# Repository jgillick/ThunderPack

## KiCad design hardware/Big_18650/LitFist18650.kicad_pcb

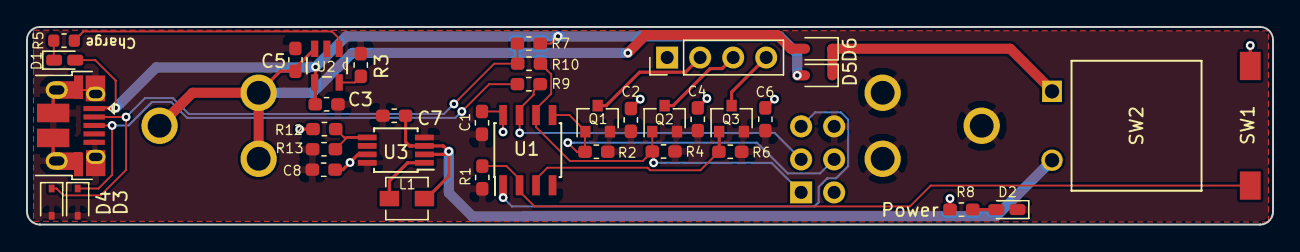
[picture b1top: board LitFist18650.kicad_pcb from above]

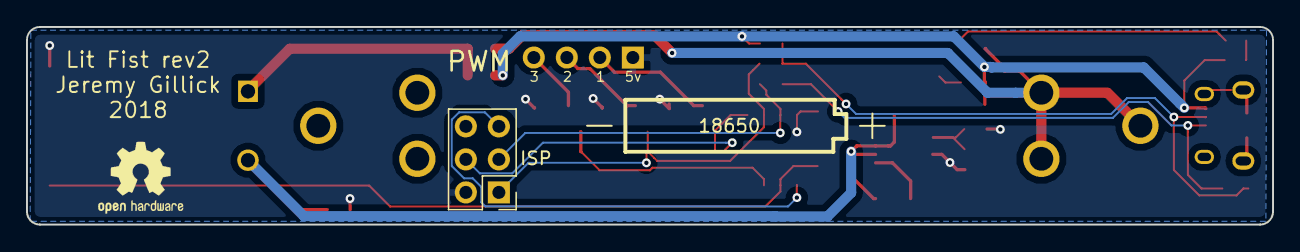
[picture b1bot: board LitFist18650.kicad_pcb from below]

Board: 2 copper layers, 95.8 x 15.2 mm, 39 parts (2 on the bottom side), 23 nets.

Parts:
C1: 0.1uF; C_0603_1608Metric_Pad1.05x0.95mm_HandSolder
C2, C3, C4, C5, C6: 4.7uF; C_0603_1608Metric_Pad1.05x0.95mm_HandSolder
C7: 10uF; C_0603_1608Metric_Pad1.05x0.95mm_HandSolder
C8: 22uF; C_0603_1608Metric_Pad1.05x0.95mm_HandSolder
D1, D2: LED; LED_0603_1608Metric_Castellated
D3, D4: 3v6; D_SOD-323
D5, D6: 20V2A; D_SOD-323
J1: PWM; PinHeader_1x04_P2.54mm_Vertical
J2: USB_B_Micro; USB_Micro-B_Amphenol_10103594-0001LF_Horizontal
J3: Battery; Battery_Clips_18650
J4: ISP; PinHeader_2x03_P2.54mm_Vertical
L1: 2.2uH3A; L_Vishay_IHLP-1212
Q1, Q2, Q3: NTR4003NT1G; SOT-23
R1: 20K; R_0603_1608Metric_Pad1.05x0.95mm_HandSolder
R2, R4, R6: 20k; R_0603_1608Metric_Pad1.05x0.95mm_HandSolder
R3: 2k; R_0603_1608Metric_Pad1.05x0.95mm_HandSolder
R5: 470; R_0603_1608Metric
R7: 2.2k; R_0603_1608Metric_Pad1.05x0.95mm_HandSolder
R8: 120; R_0603_1608Metric_Pad1.05x0.95mm_HandSolder
R9, R10: 68; R_0603_1608Metric_Pad1.05x0.95mm_HandSolder
R12: 750K; R_0603_1608Metric_Pad1.05x0.95mm_HandSolder
R13: 100K; R_0603_1608Metric_Pad1.05x0.95mm_HandSolder
SW1: Mode; Switch_TE_FSMSM
SW2: Power; Switch_SPST_GPTS203211BR2
U1: ATtiny85-20SU; SOIC-8_3.9x4.9mm_P1.27mm
U2: MCP73831T-2ACI/OT; SOT95P280X145-5N
U3: PAM2401-8MSOP; MSOP-8_3x3mm_P0.65mm

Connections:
+5V: C1.1, C2.2, C4.2, C6.2, C8.1, J1.1, J4.2, R8.2, R12.1, SW1.1, U1.8, U3.7
+BATT: C5.1, D6.2, J3.1, U2.3
D+: J4.3, R9.1, U1.7
D-: J4.1, Q2.1, R4.1, R10.1, U1.6
GND: C1.2, C2.1, C3.2, C4.1, C5.2, C6.1, C7.2, C8.2, D2.1, D3.2, D4.2, J2.5, J2.6, J3.2, J4.6, Q1.2, Q2.2, Q3.2, R1.2, R2.2, R3.2, R4.2, R6.2, R13.2, U1.4, U2.2, U3.4, U3.8
MOSI: J4.4, Q1.1, R2.1, U1.5
unnamed: C7.1, L1.1, SW2.2, U3.2, U3.3
unnamed: D1.1, R5.2
unnamed: D2.2, R8.1
unnamed: D3.1, J2.3, R9.2
unnamed: D4.1, J2.2, R7.1, R10.2
unnamed: D5.1, D6.1, SW2.1
unnamed: J1.2, Q1.3
unnamed: J1.3, Q2.3
unnamed: J1.4, Q3.3
unnamed: L1.2, U3.1
unnamed: R1.1, SW1.2, U1.2
unnamed: R3.1, U2.5
unnamed: R5.1, U2.1
unnamed: R12.2, R13.1, U3.5
PWM3: Q3.1, R6.1, U1.3
RST: J4.5, U1.1
Vin: C3.1, D1.2, D5.2, J2.1, R7.2, U2.4
